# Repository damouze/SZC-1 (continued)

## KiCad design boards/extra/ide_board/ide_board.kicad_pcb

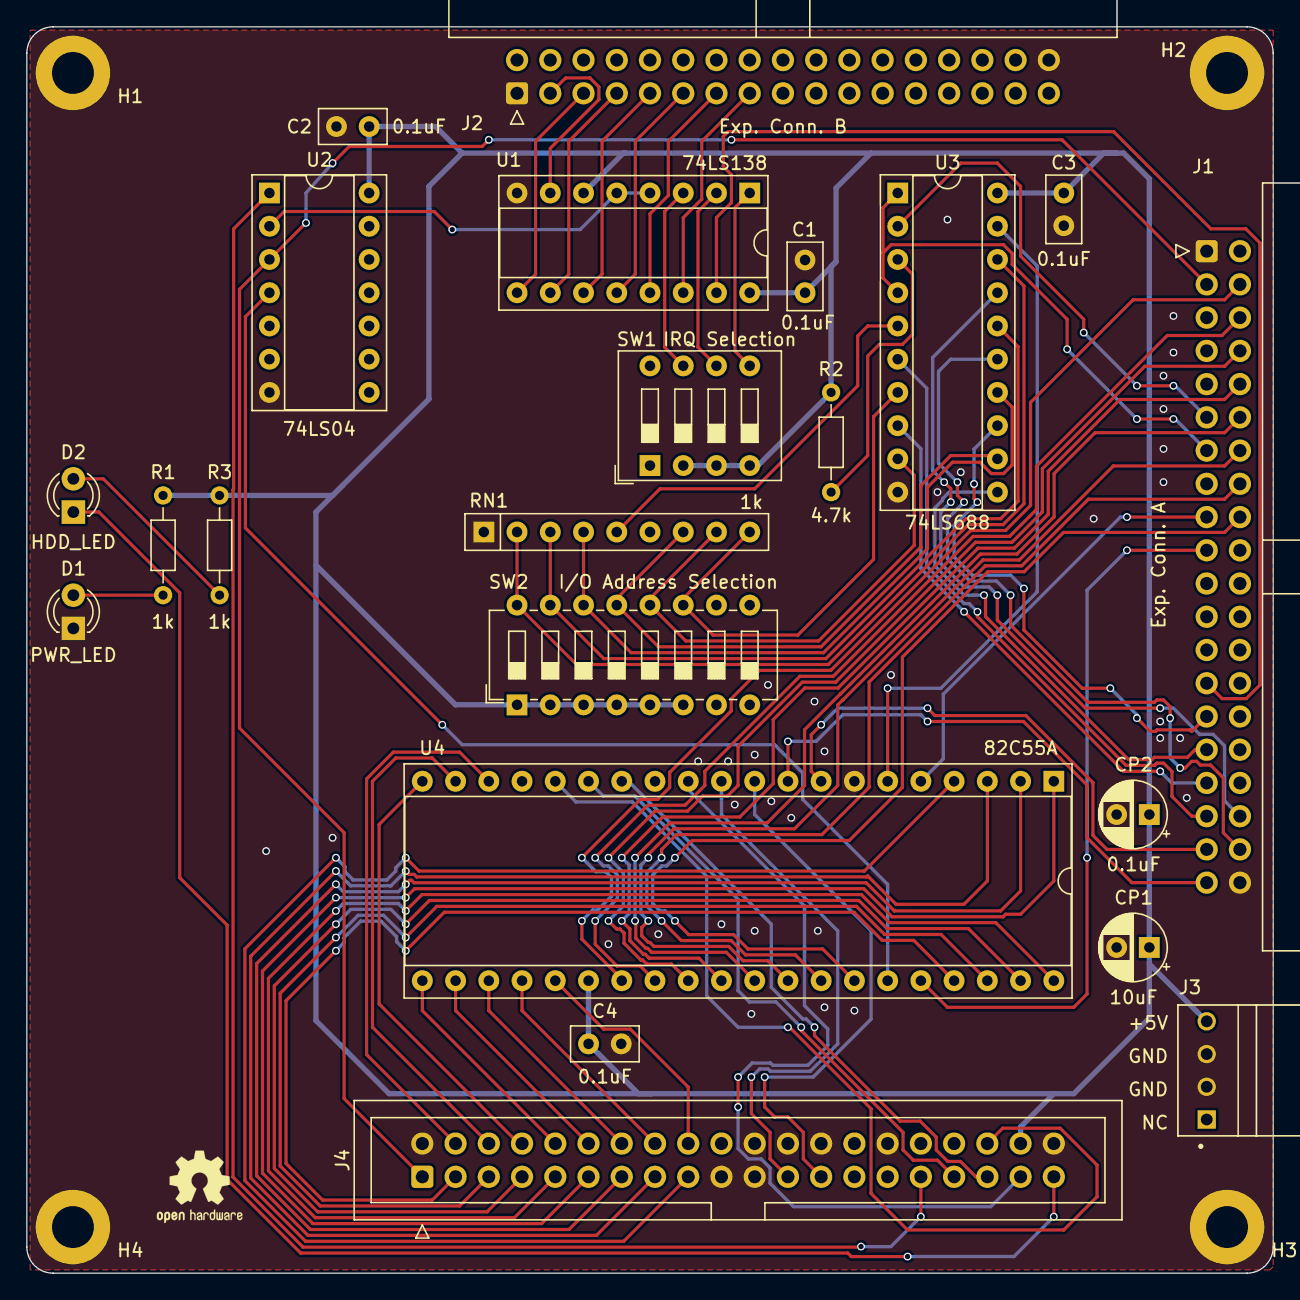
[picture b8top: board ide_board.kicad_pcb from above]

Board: 2 copper layers, 95.2 x 95.2 mm, 26 parts (0 on the bottom side), 71 nets.

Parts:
C1, C2, C3, C4: 0.1uF; C_Disc_D5.0mm_W2.5mm_P2.50mm
CP1: 10uF; CP_Radial_D5.0mm_P2.50mm
CP2: 0.1uF; CP_Radial_D5.0mm_P2.50mm
D1: PWR_LED; LED_D3.0mm
D2: HDD_LED; LED_D3.0mm
H1, H2, H3, H4: MountingHole_Pad; MountingHole_3.2mm_M3_ISO7380_Pad
J1: Exp. Conn. A; IDC-Header_2x20_P2.54mm_Horizontal
J2: Exp. Conn. B; IDC-Header_2x17_P2.54mm_Horizontal
J3: Power; TE_171826-4
J4: IDE; IDC-Header_2x20_P2.54mm_Vertical
R1, R3: 1k; R_Axial_DIN0204_L3.6mm_D1.6mm_P7.62mm_Horizontal
R2: 4.7k; R_Axial_DIN0204_L3.6mm_D1.6mm_P7.62mm_Horizontal
RN1: 1k; R_Array_SIP9
SW1: IRQ Selection; SW_DIP_SPSTx04_Slide_9.78x12.34mm_W7.62mm_P2.54mm
SW2: I/O Address Selection; SW_DIP_SPSTx08_Slide_6.7x21.88mm_W7.62mm_P2.54mm_LowProfile
U1: 74LS138; DIP-16_W7.62mm_Socket
U2: 74LS04; DIP-14_W7.62mm_Socket
U3: 74LS688; DIP-20_W7.62mm_Socket
U4: 82C55A; DIP-40_W15.24mm_Socket

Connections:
/+5V: C1.1, C2.1, C3.1, C4.1, CP1.1, CP2.1, J3.4, J4.38, R1.1, R2.2, R3.1, SW1.2, SW1.3, SW1.4, SW2.1, SW2.2, SW2.3, SW2.4, SW2.5, SW2.6, U1.6 (E3), U1.16 (VCC), U2.14 (VCC), U3.20 (VCC), U4.26 (VCC)
/B_A0: J1.39, U4.9 (A0)
/B_A1: J1.37, U4.8 (A1)
/B_A2: J1.35, U3.6 (P2)
/B_A3: J1.33, U3.8 (P3)
/B_A4: J1.31, U3.11 (P4)
/B_A5: J1.29, U3.13 (P5)
/B_A6: J1.38, U3.15 (P6)
/B_A7: J1.36, U3.17 (P7)
/B_D0: J1.18, U4.34 (D0)
/B_D1: J1.16, U4.33 (D1)
/B_D2: J1.14, U4.32 (D2)
/B_D3: J1.12, U4.31 (D3)
/B_D4: J1.10, U4.30 (D4)
/B_D5: J1.8, U4.29 (D5)
/B_D6: J1.6, U4.28 (D6)
/B_D7: J1.4, U4.27 (D7)
/GND: C1.2, C2.2, C3.2, C4.2, CP1.2, CP2.2, D1.1 (K), H1.1, H2.1, H3.1, H4.1, J1.1, J1.40, J2.1, J2.34, J3.2, J3.3, J4.2, J4.19, J4.21, J4.22, J4.24, J4.26, J4.30, J4.40, RN1.1 (common), U1.8 (GND), U2.7 (GND), U3.10 (GND), U4.7 (GND)
/HA0: J4.35, U4.14 (PC0)
/HA1: J4.33, U4.15 (PC1)
/HA2: J4.36, U4.16 (PC2)
/HD0: J4.17, U4.4 (PA0)
/HD1: J4.15, U4.3 (PA1)
/HD2: J4.13, U4.2 (PA2)
/HD3: J4.11, U4.1 (PA3)
/HD4: J4.9, U4.40 (PA4)
/HD5: J4.7, U4.39 (PA5)
/HD6: J4.5, U4.38 (PA6)
/HD7: J4.3, U4.37 (PA7)
/HD8: J4.4, U4.18 (PB0)
/HD9: J4.6, U4.19 (PB1)
/HD10: J4.8, U4.20 (PB2)
/HD11: J4.10, U4.21 (PB3)
/HD12: J4.12, U4.22 (PB4)
/HD13: J4.14, U4.23 (PB5)
/HD14: J4.16, U4.24 (PB6)
/HD15: J4.18, U4.25 (PB7)
/HDD_LED: D2.1 (K), J4.39
/IDE_RESET: U2.4, U4.35 (RESET)
/IRQ: J4.31, U2.1
/IRQ0_S: SW1.5, U1.1 (A0)
/IRQ1_S: SW1.6, U1.2 (A1)
/IRQ2_S: SW1.7, U1.3 (A2)
/R_A2: RN1.9 (R8), SW2.11, U3.7 (R2)
/R_A3: RN1.8 (R7), SW2.12, U3.9 (R3)
/R_A4: RN1.7 (R6), SW2.13, U3.12 (R4)
/R_A5: RN1.4 (R3), SW2.14, U3.14 (R5)
/R_A6: RN1.3 (R2), SW2.15, U3.16 (R6)
/R_A7: RN1.2 (R1), SW2.16, U3.18 (R7)
/~B_IORQ: J1.13, U3.1 (G), U3.4 (P1)
/~B_M1: J1.11, U3.2 (P0)
/~B_RD: J1.19, U4.36 (~WR)
/~B_WR: J1.17, U4.5 (~RD)
/~HCS0: J4.37, U4.12 (PC5)
/~HRD: J4.25, U4.10 (PC7)
/~HWR: J4.23, U4.11 (PC6)
/~IDE_CS: U3.19 (P=R), U4.6 (~CS)
/~INT1: J2.15, U1.14 (O1)
/~INT2: J2.13, U1.13 (O2)
/~INT3: J2.11, U1.12 (O3)
/~INT4: J2.9, U1.11 (O4)
/~INT5: J2.7, U1.10 (O5)
/~INT6: J2.5, U1.9 (O6)
/~INT7: J2.3, U1.7 (O7)
/~INT: J1.27, U1.15 (O0)
/~IRQ: U1.4 (E1), U1.5 (E2), U2.2
/~RESET: J1.3, J4.1, U2.3
/~R_IORQ: RN1.5 (R4), U3.5 (R1)
/~R_M1: R2.1, U3.3 (R0)
unnamed: D1.2 (A), R1.2
unnamed: D2.2 (A), R3.2

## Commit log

2023-10-09 Initial commit.
2023-10-09 Moved boards/rom_ram_board_2MB to boards/extra/rom_ram_board_2MB
2023-10-14 Removed BOM-files received from PCBWay.
2023-10-14 Generated interactive BOMs for most boards.
2023-10-14 Added description for ibom folder to README.md
2023-10-21 Commit latest changes.
2023-12-30 * Working on new powerdistribution method.
2024-03-14 Added expansion connector C and designed some new boards around it.
2024-03-14 Added new expansion connector C.
2024-03-14 Added audio board.
2024-03-15 Removed CPU connection A14 and A15 from Expansion Bus Connector B.
2024-03-16 Added 128kB ROM/RAM board v2.
2024-03-16 Added rom_ram_board_128kB_v2 to README.md
2024-04-24 Preparation for ordering with PCBWay.
2024-04-24 Preparation for assembly order with PCBWay
2024-04-25 Changed footprint of D2 to DO-35.
2024-05-04 Final commmit before upgrade to KiCad 8.0.x.
2024-05-04 Upgraded board to KiCad 8 and imported design rules from the PCBWay website.
2024-08-14 Updated ROM/RAM Board V2
    Updated the ROM/RAM Board V2 to revision 1.1
2024-08-14 Added new renderings
    Added some new renderings.
2024-08-14 Updated CPU board V2 with extension bus
2024-08-14 Added Poweboard V2
    Added Powerboard V2, which has power-on circuitry onboard.
2024-08-14 Added new IBOMs
2024-08-14 Added Simple I/O board
2024-08-14 Updated IDE board
2024-08-14 Updated Audio board
2024-08-14 Updated diag board
2024-08-14 Updated PIC board
2024-09-09 Updated serial I/O board last weekend.
2025-08-22 New build workflow for the MMU
2025-08-22 Cleaning up old files
2025-08-22 Cleaning up old files some more.
2025-08-22 Genera update of renderings and specifications
2025-08-22 Extended CPU board update
